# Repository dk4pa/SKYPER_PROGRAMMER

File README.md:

# SKYPER_PROGRAMMER
Programmer PCB for Skyper Pager e.g. NEC21A

# Connection to Pager

The connection to the pager is realized by 4 wires (GND, RX, TX, EN). These need to be connected as outlined in the picture.

## Version

### v0.1

First THT version produced with Kicad 

### v0.2
SMD Version to be mounted inside a RS-232 Plug case and powered by USB cable. There is a [Mouser Cart]( https://www.mouser.com/ProjectManager/ProjectDetail.aspx?AccessID=938ca9dcb5) for the parts except the 2.54mm pins and Sub-D 9 connector.

## License

This project is released under the Creative Commons Attribution-NonCommercial-ShareAlike 3.0 (CC-BY-NC-SA 3.0, https://creativecommons.org/licenses/by-nc-sa/3.0/) license. You may edit and share it as you like, as long as credit is given and the license is not changed. You can build as many boards for you and your friends as you like and you can even sell it to them to cover your costs, however it is strictly forbidden to turn this into a commercial product! You are not allowed to build and sell these boards for profit!

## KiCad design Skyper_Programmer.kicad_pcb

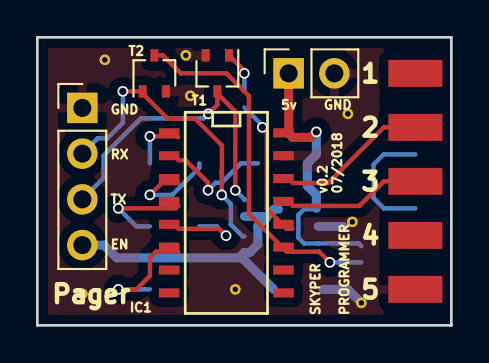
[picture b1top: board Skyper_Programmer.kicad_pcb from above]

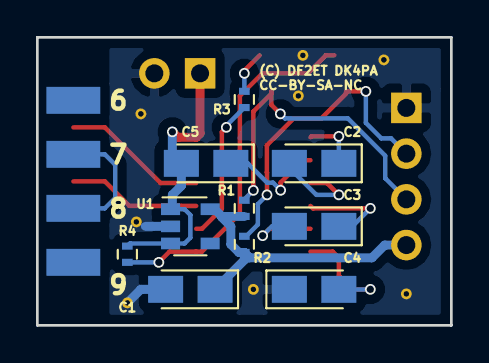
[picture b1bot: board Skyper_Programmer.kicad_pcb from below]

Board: 2 copper layers, 23.0 x 16.0 mm, 24 parts (14 on the bottom side), 17 nets.

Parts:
C1: 10µF; CP_Tantalum_Case-A_EIA-3216-18_Reflow
C2, C3, C4, C5: 1µF; CP_Tantalum_Case-A_EIA-3216-18_Reflow
IC1: MAX232; SO-16-N
J1: Pager; PinHeader_1x04_P2.54mm_Vertical
J2: USB PWR; PinSocket_1x02_P2.54mm_Vertical
J3: Pin1; SubD Pad
J4: Pin6; SubD Pad
J5: Pin2; SubD Pad
J6: Pin7; SubD Pad
J7: Pin3; SubD Pad
J8: Pin8; SubD Pad
J9: Pin4; SubD Pad
J10: Pin9; SubD Pad
J11: Pin5; SubD Pad
R1, R3, R4: 10k; R_0402
R2: 47k; R_0402
T1, T2: BC847; SOT-323_SC-70
U1: TC1055; SOT-23-5

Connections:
+3V0: C1.1, J1.4, R1.2, R2.2, U1.5
+5V: C5.2, IC1.16, J2.1, R4.2, U1.1, U1.3
GND: C1.2, C4.1, IC1.15, J1.1, J2.2, J11.1, T1.2, T2.2, U1.2
unnamed: C2.1, IC1.1
unnamed: C2.2, IC1.3
unnamed: C3.1, IC1.4
unnamed: C3.2, IC1.5
unnamed: C4.2, IC1.6
unnamed: C5.1, IC1.2
unnamed: IC1.11, R4.1, T2.3
unnamed: IC1.12, R3.1
unnamed: IC1.13, J7.1
unnamed: IC1.14, J5.1
unnamed: J1.2, R2.1, T2.1
unnamed: J1.3, R1.1, T1.3
unnamed: J6.1, J8.1
unnamed: R3.2, T1.1

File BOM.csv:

Refs,Value,Footprint,QTY,MFR,MPN,SPR,SPN
C1,10u,Capacitors_Tantalum_SMD:CP_Tantalum_Case-A_EIA-3216-18_Reflow,1,AVX,F931C106KAA,Mouser,647-F931C106KAA
C2;C3;C5;C4,1u,Capacitors_Tantalum_SMD:CP_Tantalum_Case-A_EIA-3216-18_Reflow,4,AVX,F931C105MAA,Mouser,647-F931C105MAA
J1,Pager,Connector_PinHeader_2.54mm:PinHeader_1x04_P2.54mm_Vertical,1,,,,
J2,USB PWR,Connector_PinSocket_2.54mm:PinSocket_1x02_P2.54mm_Vertical,1,,,,
U1,TC1055,Package_TO_SOT_SMD:SOT-23-5,1,https://www.mouser.de/datasheet/2/268/21350c-61546.pdf,TC1055-3.0VCT713,Mouser,579-TC1055-3.0VCT713
R3;R1;R4,10k,Resistors_SMD:R_0402,3,Panasonic,ERJ-PA2F1002X,Mouser,667-ERJ-PA2F1002X
R2,47k,Resistors_SMD:R_0402,1,Panasonic,ERJ-PA2F4702X,Mouser,667-ERJ-PA2F4702X
IC1,MAX232,SMD_Packages:SO-16-N,1,Maxim Integrated,MAX232ESE+,Mouser,700-MAX232ESE
J3,Pin1,SubD_Connector:SubD Pad,1,,,,
J5,Pin2,SubD_Connector:SubD Pad,1,,,,
J7,Pin3,SubD_Connector:SubD Pad,1,,,,
J9,Pin4,SubD_Connector:SubD Pad,1,,,,
J11,Pin5,SubD_Connector:SubD Pad,1,,,,
J4,Pin6,SubD_Connector:SubD Pad,1,,,,
J6,Pin7,SubD_Connector:SubD Pad,1,,,,
J8,Pin8,SubD_Connector:SubD Pad,1,,,,
J10,Pin9,SubD_Connector:SubD Pad,1,,,,
T1;T2,BC847,TO_SOT_Packages_SMD:SOT-323_SC-70,2,ON Semiconductor,SBC847AWT1G,Mouser,863-SBC847AWT1G

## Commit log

2018-04-30 Update Files
2018-05-20 Change parts to SMD
2018-05-21 Add some Text to PCB
2018-05-21 Update formatting
2018-05-21 Update meta data and add PDF plot
2018-05-21 Change Image to front view
2018-05-21 Add BOM data
2018-05-21 Add netlist
2018-05-21 Add BOM lists
2018-05-21 Add Mouser cart to README
2018-07-10 Change pin header labelling
2018-07-11 Update pic and meta data
2018-07-11 Update picture
2018-08-08 Add picture for pinout / connection
2018-08-08 Correct link

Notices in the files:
Skyper_Programmer.kicad_pcb:
CC-BY-SA-NC
